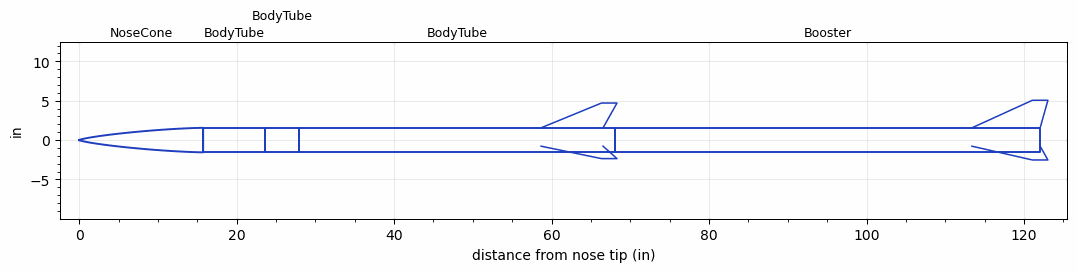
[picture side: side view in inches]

<RASAeroDocument>
 <FileVersion>2</FileVersion>
 <RocketDesign>
  <NoseCone>
   <Length>15.748</Length>
   <Diameter>3.1102</Diameter>
   <Shape>Von Karman Ogive</Shape>
   <Location>0</Location>
  </NoseCone>
  <BodyTube>
   <Length>7.874</Length>
   <Diameter>3.1102</Diameter>
   <Location>15.748</Location>
  </BodyTube>
  <BodyTube>
   <Length>4.3307</Length>
   <Diameter>3.1102</Diameter>
   <Location>23.622</Location>
  </BodyTube>
  <BodyTube>
   <Length>40.1574</Length>
   <Diameter>3.1102</Diameter>
   <Location>27.9527</Location>
   <Fin>
    <Count>3</Count>
    <Chord>7.874</Chord>
    <Span>3.1496</Span>
    <SweepDistance>7.6772</SweepDistance>
    <TipChord>1.9685</TipChord>
    <Thickness>0.125</Thickness>
    <Location>9.4488</Location>
    <AirfoilSection>Rounded</AirfoilSection>
   </Fin>
  </BodyTube>
  <Booster>
   <Length>53.9369</Length>
   <Diameter>3.1102</Diameter>
   <InsideDiameter>3.1102</InsideDiameter>
   <Location>68.1101</Location>
   <ShoulderLength>0</ShoulderLength>
   <Fin>
    <Count>3</Count>
    <Chord>8.6614</Chord>
    <Span>3.5</Span>
    <SweepDistance>7.6772</SweepDistance>
    <TipChord>1.9685</TipChord>
    <Thickness>0.125</Thickness>
    <Location>8.6614</Location>
    <AirfoilSection>Rounded</AirfoilSection>
   </Fin>
  </Booster>
  <Surface>Sheet Metal</Surface>
  <ModifiedBarrowman>False</ModifiedBarrowman>
  <Turbulence>False</Turbulence>
  <UseBooster1>True</UseBooster1>
  <UseBooster2>False</UseBooster2>
 </RocketDesign>
 <LaunchSite>
  <Altitude>1249</Altitude>
  <Pressure>29.92</Pressure>
  <RodAngle>0</RodAngle>
  <RodLength>39.37</RodLength>
  <Temperature>59</Temperature>
  <WindSpeed>4.47</WindSpeed>
 </LaunchSite>
 <Recovery>
  <Altitude1>656.168</Altitude1>
  <Altitude2>656.168</Altitude2>
  <DeviceType1>Parachute</DeviceType1>
  <DeviceType2>Parachute</DeviceType2>
  <Event1>True</Event1>
  <Event2>True</Event2>
  <Size1>39.9999</Size1>
  <Size2>15</Size2>
  <EventType1>Altitude</EventType1>
  <EventType2>Apogee</EventType2>
  <CD1>0.8</CD1>
  <CD2>0</CD2>
 </Recovery>
 <SimulationList>
  <Simulation>
   <SustainerEngine>M1315W  (AT)</SustainerEngine>
   <SustainerLaunchWt>17.7</SustainerLaunchWt>
   <SustainerNozzleDiameter>2.4</SustainerNozzleDiameter>
   <SustainerCG>46.71</SustainerCG>
   <SustainerIgnitionDelay>13.24</SustainerIgnitionDelay>
   <Booster1Engine>M1315W  (AT)</Booster1Engine>
   <Booster1LaunchWt>34.81</Booster1LaunchWt>
   <Booster1SeparationDelay>1</Booster1SeparationDelay>
   <Booster1IgnitionDelay>0</Booster1IgnitionDelay>
   <Booster1CG>73.81</Booster1CG>
   <Booster1NozzleDiameter>2.4</Booster1NozzleDiameter>
   <IncludeBooster1>True</IncludeBooster1>
   <Booster2Delay>0</Booster2Delay>
   <IncludeBooster2>False</IncludeBooster2>
   <TimetoApogee>95.05048</TimetoApogee>
   <MaxAltitude>115718.3</MaxAltitude>
   <MaxVelocity>3596.063</MaxVelocity>
  </Simulation>
  <Simulation>
   <SustainerEngine>L645-GR-P  (CTI)</SustainerEngine>
   <SustainerLaunchWt>13.53</SustainerLaunchWt>
   <SustainerNozzleDiameter>0.9</SustainerNozzleDiameter>
   <SustainerCG>48.76</SustainerCG>
   <SustainerIgnitionDelay>9.67</SustainerIgnitionDelay>
   <Booster1Engine>L645-GR-P  (CTI)</Booster1Engine>
   <Booster1LaunchWt>26.46</Booster1LaunchWt>
   <Booster1SeparationDelay>1</Booster1SeparationDelay>
   <Booster1IgnitionDelay>0</Booster1IgnitionDelay>
   <Booster1CG>75.95</Booster1CG>
   <Booster1NozzleDiameter>0.9</Booster1NozzleDiameter>
   <IncludeBooster1>True</IncludeBooster1>
   <Booster2Delay>0</Booster2Delay>
   <IncludeBooster2>False</IncludeBooster2>
   <TimetoApogee>50.73862</TimetoApogee>
   <MaxAltitude>32022.08</MaxAltitude>
   <MaxVelocity>1893.035</MaxVelocity>
  </Simulation>
  <Simulation>
   <SustainerEngine>K780R  (AT)</SustainerEngine>
   <SustainerLaunchWt>11.72</SustainerLaunchWt>
   <SustainerNozzleDiameter>0.5</SustainerNozzleDiameter>
   <SustainerCG>47.1</SustainerCG>
   <SustainerIgnitionDelay>0.08</SustainerIgnitionDelay>
   <Booster1Engine>K780R  (AT)</Booster1Engine>
   <Booster1LaunchWt>22.86</Booster1LaunchWt>
   <Booster1SeparationDelay>1</Booster1SeparationDelay>
   <Booster1IgnitionDelay>0</Booster1IgnitionDelay>
   <Booster1CG>74.27</Booster1CG>
   <Booster1NozzleDiameter>0.5</Booster1NozzleDiameter>
   <IncludeBooster1>True</IncludeBooster1>
   <Booster2Delay>0</Booster2Delay>
   <IncludeBooster2>False</IncludeBooster2>
   <TimetoApogee>32.92056</TimetoApogee>
   <MaxAltitude>19642.89</MaxAltitude>
   <MaxVelocity>1766.245</MaxVelocity>
  </Simulation>
  <Simulation>
   <SustainerEngine>M650W  (AT)</SustainerEngine>
   <SustainerLaunchWt>16.55</SustainerLaunchWt>
   <SustainerNozzleDiameter>1.3</SustainerNozzleDiameter>
   <SustainerCG>46.32</SustainerCG>
   <SustainerIgnitionDelay>3.96</SustainerIgnitionDelay>
   <Booster1Engine>L1150  (AT)</Booster1Engine>
   <Booster1LaunchWt>29.32</Booster1LaunchWt>
   <Booster1SeparationDelay>1</Booster1SeparationDelay>
   <Booster1IgnitionDelay>0</Booster1IgnitionDelay>
   <Booster1CG>71.31</Booster1CG>
   <Booster1NozzleDiameter>0.6</Booster1NozzleDiameter>
   <IncludeBooster1>True</IncludeBooster1>
   <Booster2Delay>0</Booster2Delay>
   <IncludeBooster2>False</IncludeBooster2>
   <TimetoApogee>56.19728</TimetoApogee>
   <MaxAltitude>53319.24</MaxAltitude>
   <MaxVelocity>2452.721</MaxVelocity>
  </Simulation>
  <Simulation>
   <SustainerEngine>L2200G  (AT)</SustainerEngine>
   <SustainerLaunchWt>16.2</SustainerLaunchWt>
   <SustainerNozzleDiameter>2.5</SustainerNozzleDiameter>
   <SustainerCG>46.96</SustainerCG>
   <SustainerIgnitionDelay>6</SustainerIgnitionDelay>
   <Booster1Engine>L2200G  (AT)</Booster1Engine>
   <Booster1LaunchWt>31.8</Booster1LaunchWt>
   <Booster1SeparationDelay>0.5</Booster1SeparationDelay>
   <Booster1IgnitionDelay>0</Booster1IgnitionDelay>
   <Booster1CG>74.65</Booster1CG>
   <Booster1NozzleDiameter>2.5</Booster1NozzleDiameter>
   <IncludeBooster1>True</IncludeBooster1>
   <Booster2Delay>0</Booster2Delay>
   <IncludeBooster2>False</IncludeBooster2>
   <TimetoApogee>52.3877</TimetoApogee>
   <MaxAltitude>49870.34</MaxAltitude>
   <MaxVelocity>3183.107</MaxVelocity>
  </Simulation>
 </SimulationList>
</RASAeroDocument>
